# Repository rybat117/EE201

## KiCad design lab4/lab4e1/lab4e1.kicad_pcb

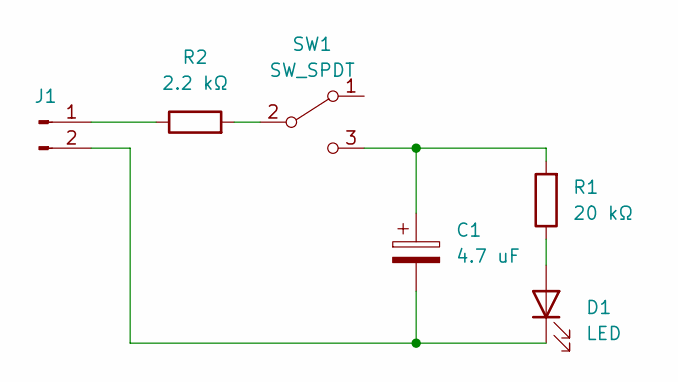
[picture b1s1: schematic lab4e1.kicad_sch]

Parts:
C1: 4.7 uF
D1: LED
J1: 9.1 V
R1: 20 kΩ
R2: 2.2 kΩ
SW1: SW_SPDT

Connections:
unnamed: C1.1, R1.2, SW1.3 (C)
unnamed: C1.2, D1.1 (K), J1.2
unnamed: D1.2 (A), R1.1
unnamed: J1.1, R2.1
unnamed: R2.2, SW1.2 (B)

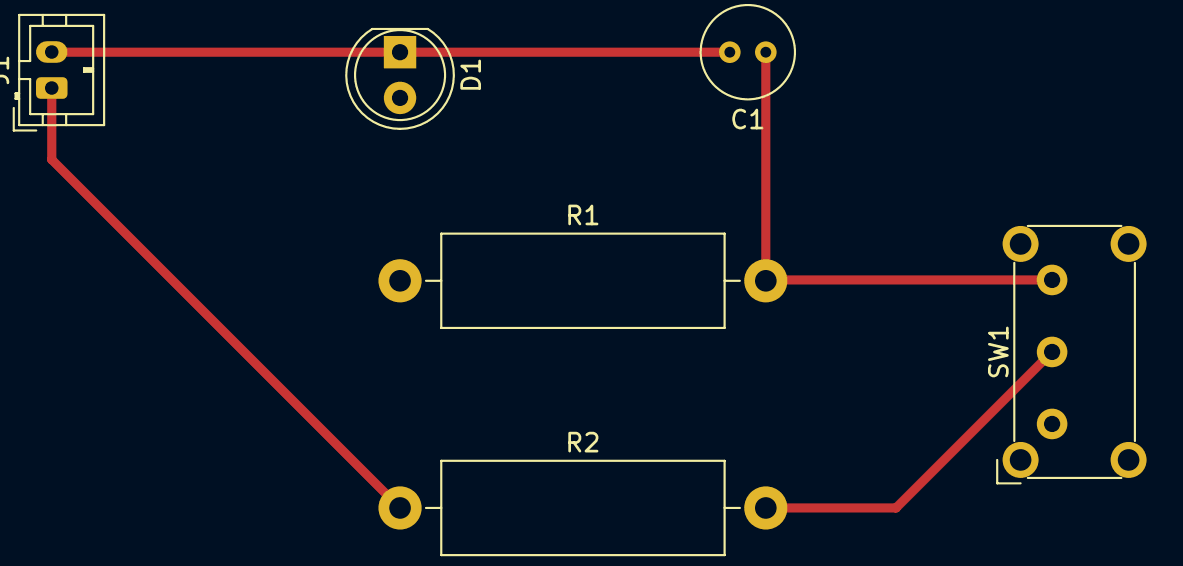
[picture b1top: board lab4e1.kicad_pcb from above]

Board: 2 copper layers, 6 parts (0 on the bottom side), 5 nets.

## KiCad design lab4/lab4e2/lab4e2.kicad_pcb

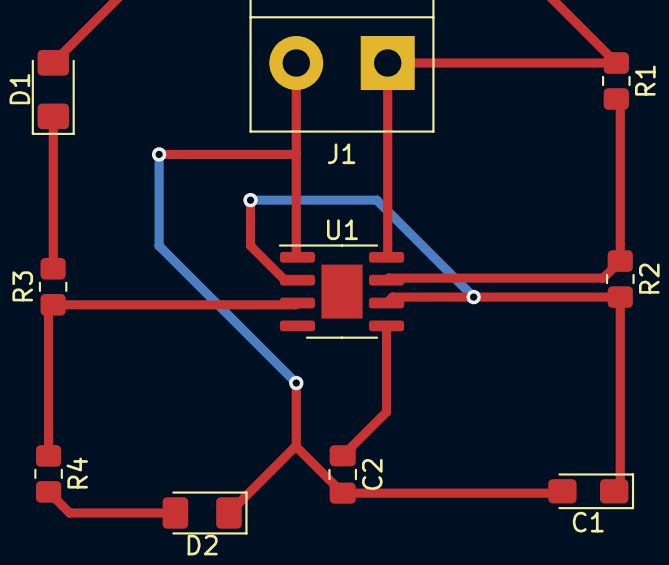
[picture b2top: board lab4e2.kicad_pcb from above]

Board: 2 copper layers, 10 parts (0 on the bottom side), 8 nets.

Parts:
C1: 10uF; CP_EIA-3216-18_Kemet-A_Pad1.58x1.35mm_HandSolder
C2: 0.01 uF; C_0805_2012Metric_Pad1.18x1.45mm_HandSolder
D1, D2: LED; LED_1206_3216Metric_Pad1.42x1.75mm_HandSolder
J1: Conn_01x02_Male; TerminalBlock_bornier-2_P5.08mm
R1, R3, R4: 1k; R_0805_2012Metric_Pad1.20x1.40mm_HandSolder
R2: 10k; R_0805_2012Metric_Pad1.20x1.40mm_HandSolder
U1: NE555D; SOIC-8-1EP_3.9x4.9mm_P1.27mm_EP2.29x3mm

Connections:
+9V: D1.2 (A), J1.1, R1.1, U1.8 (VCC)
/pin2: C1.1, R2.2, U1.2 (TR), U1.6 (THR)
/pin3: R3.1, R4.1, U1.3 (Q)
GND: C1.2, C2.2, D2.1 (K), J1.2, U1.1 (GND)
unnamed: C2.1, U1.5 (CV)
unnamed: D1.1 (K), R3.2
unnamed: D2.2 (A), R4.2
unnamed: R1.2, R2.1, U1.7 (DIS)

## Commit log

2023-01-12 made readme
2023-01-12 please
2023-01-19 added lab 3 files
2023-01-26 got them lab4 in there m8
2023-02-02 made new branch
2023-02-02 added lab 5
2023-02-09 i think i added lab 6?
2023-02-16 added gerber/drill files
2023-03-09 final image, also completed lab demo
